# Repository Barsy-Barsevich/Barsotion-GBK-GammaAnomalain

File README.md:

# Barsotion GBK GammaAnomalain

Board computer created for "OKB Iva "Kilka"", 2024

## Parameters
- Microcontroller: ATmega328PB / LGT8X328P
- Clock frequency: 16MHz / 32MHz
- Gyroscope: external, MPU6050 (I2C)
- Barometer: external, 2x BMP388 (I2C)
- Memory: 8MB SPI NOR Flash

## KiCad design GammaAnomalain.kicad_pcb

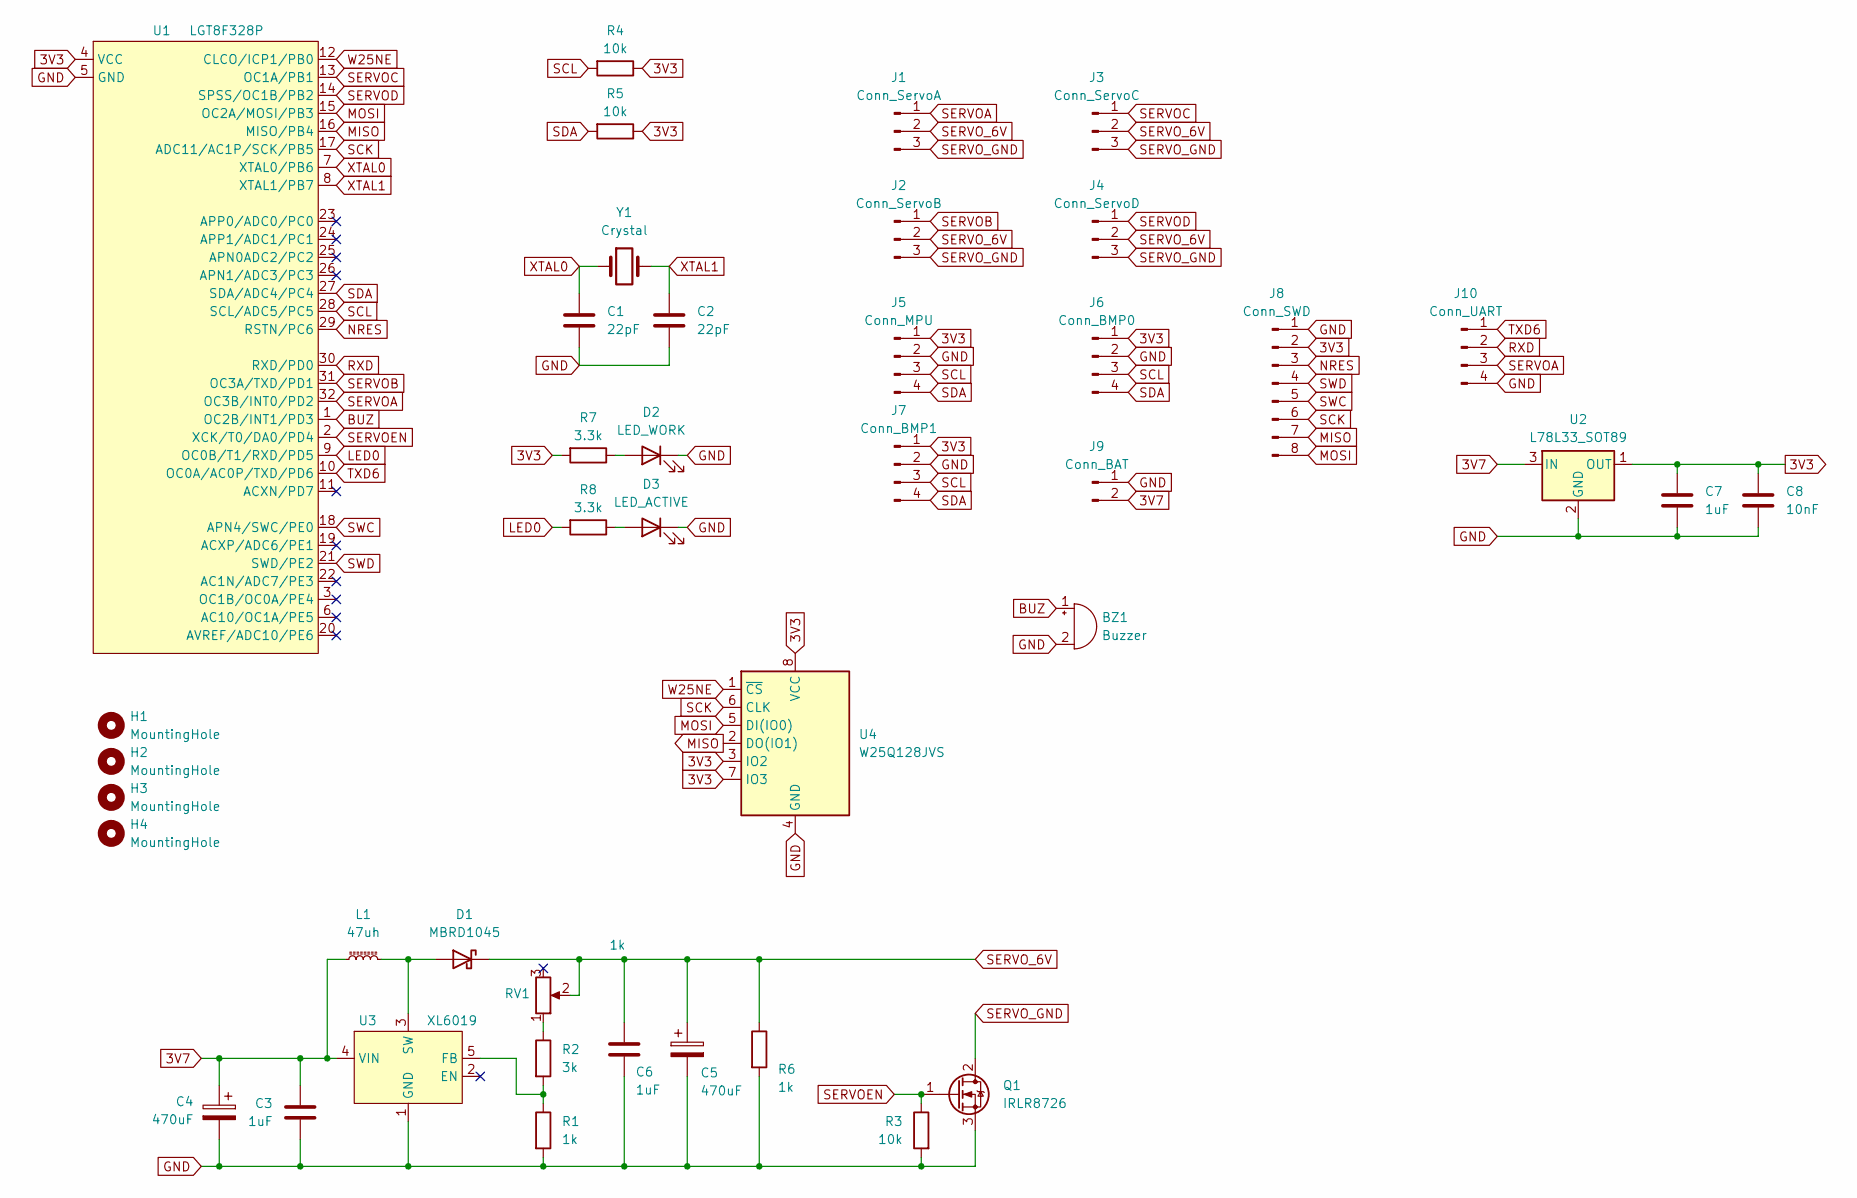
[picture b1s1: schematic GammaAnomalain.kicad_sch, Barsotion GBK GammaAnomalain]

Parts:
BZ1: Buzzer; MagneticBuzzer_ProSignal_ABI-009-RC
C1, C2: 22pF; C_0805_2012Metric
C3, C6, C7: 1uF; C_1206_3216Metric_Pad1.33x1.80mm_HandSolder
C4, C5: 470uF; CP_Radial_D8.0mm_P3.50mm
C8: 10nF; C_0805_2012Metric_Pad1.18x1.45mm_HandSolder
D1: MBRD1045; TO-252-2_TabPin1_Other2
D2: LED_WORK; LED_D3.0mm
D3: LED_ACTIVE; LED_D3.0mm
H1, H2, H3, H4: MountingHole; MountingHole_3.2mm_M3
J1: Conn_ServoA; JST_XH_B3B-XH-A_1x03_P2.50mm_Vertical
J2: Conn_ServoB; JST_XH_B3B-XH-A_1x03_P2.50mm_Vertical
J3: Conn_ServoC; JST_XH_B3B-XH-A_1x03_P2.50mm_Vertical
J4: Conn_ServoD; JST_XH_B3B-XH-A_1x03_P2.50mm_Vertical
J5: Conn_MPU; JST_XH_B4B-XH-A_1x04_P2.50mm_Vertical
J6: Conn_BMP0; JST_XH_B4B-XH-A_1x04_P2.50mm_Vertical
J7: Conn_BMP1; JST_XH_B4B-XH-A_1x04_P2.50mm_Vertical
J8: Conn_SWD; PinHeader_1x08_P2.54mm_Vertical
J9: Conn_BAT; Battery_3V7_Cable_solding_connctor
J10: Conn_UART; JST_XH_B4B-XH-A_1x04_P2.50mm_Vertical
L1: 47uh; L_Toroid_Vertical_L13.0mm_W6.5mm_P5.60mm
Q1: IRLR8726; TO-252-2
R1, R6: 1k; R_0805_2012Metric_Pad1.20x1.40mm_HandSolder
R2: 3k; R_0805_2012Metric_Pad1.20x1.40mm_HandSolder
R3, R4, R5: 10k; R_0805_2012Metric_Pad1.20x1.40mm_HandSolder
R7, R8: 3.3k; R_0805_2012Metric_Pad1.20x1.40mm_HandSolder
RV1: 1k; Potentiometer_Bourns_3296W_Vertical
U1: LGT8F328P; LQFP-32_7x7mm_P0.8mm
U2: L78L33_SOT89; SOT-89-3
U3: XL6019; TO-263-5_TabPin3
U4: W25Q128JVS; DIP-8_W7.62mm_LongPads
Y1: Crystal; Crystal_HC49-4H_Vertical

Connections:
3V3: C7.1, C8.1, J5.1, J6.1, J7.1, J8.2, R4.1, R5.1, R7.2, U1.4 (VCC), U2.1 (OUT), U4.3 (IO2), U4.7 (IO3), U4.8 (VCC)
3V7: C3.1, C4.1, J9.2, L1.1, U2.3 (IN), U3.4 (VIN)
BUZ: BZ1.1 (+), U1.1 (OC2B/INT1/PD3)
GND: BZ1.2 (-), C1.2, C2.2, C3.2, C4.2, C5.2, C6.2, C7.2, C8.2, D2.1 (K), D3.1 (K), J5.2, J6.2, J7.2, J8.1, J9.1, J10.4, Q1.3 (S), R1.2, R3.2, R6.2, U1.5 (GND), U2.2 (GND), U3.1 (GND), U4.4 (GND); also elsewhere on the board
LED0: R8.2, U1.9 (OC0B/T1/RXD/PD5)
MISO: J8.7, U1.16 (MISO/PB4), U4.2 (DO(IO1))
MOSI: J8.8, U1.15 (OC2A/MOSI/PB3), U4.5 (DI(IO0))
NRES: J8.3, U1.29 (RSTN/PC6)
unnamed: D1.2 (A), L1.2, U3.3 (SW)
unnamed: D2.2 (A), R7.1
unnamed: D3.2 (A), R8.1
unnamed: R2.1, RV1.1
unnamed: R1.1, R2.2, U3.5 (FB)
RXD: J10.2, U1.30 (RXD/PD0); also elsewhere on the board
SCK: J8.6, U1.17 (ADC11/AC1P/SCK/PB5), U4.6 (CLK)
SCL: J5.3, J6.3, J7.3, R4.2, U1.28 (SCL/ADC5/PC5)
SDA: J5.4, J6.4, J7.4, R5.2, U1.27 (SDA/ADC4/PC4)
SERVOA: J1.1, J10.3, U1.32 (OC3B/INT0/PD2); also elsewhere on the board
SERVOB: J2.1, U1.31 (OC3A/TXD/PD1)
SERVOC: J3.1, U1.13 (OC1A/PB1)
SERVOD: J4.1, U1.14 (SPSS/OC1B/PB2)
SERVOEN: Q1.1 (G), R3.1, U1.2 (XCK/T0/DA0/PD4)
SERVO_6V: C5.1, C6.1, D1.1 (K), J1.2, J2.2, J3.2, J4.2, R6.1, RV1.2
SERVO_GND: J1.3, J2.3, J3.3, J4.3, Q1.2 (D)
SWC: J8.5, U1.18 (APN4/SWC/PE0)
SWD: J8.4, U1.21 (SWD/PE2)
TXD6: J10.1, U1.10 (OC0A/AC0P/TXD/PD6); also elsewhere on the board
W25NE: U1.12 (CLCO/ICP1/PB0), U4.1 (~CS)
XTAL0: C1.1, U1.7 (XTAL0/PB6), Y1.1
XTAL1: C2.1, U1.8 (XTAL1/PB7), Y1.2

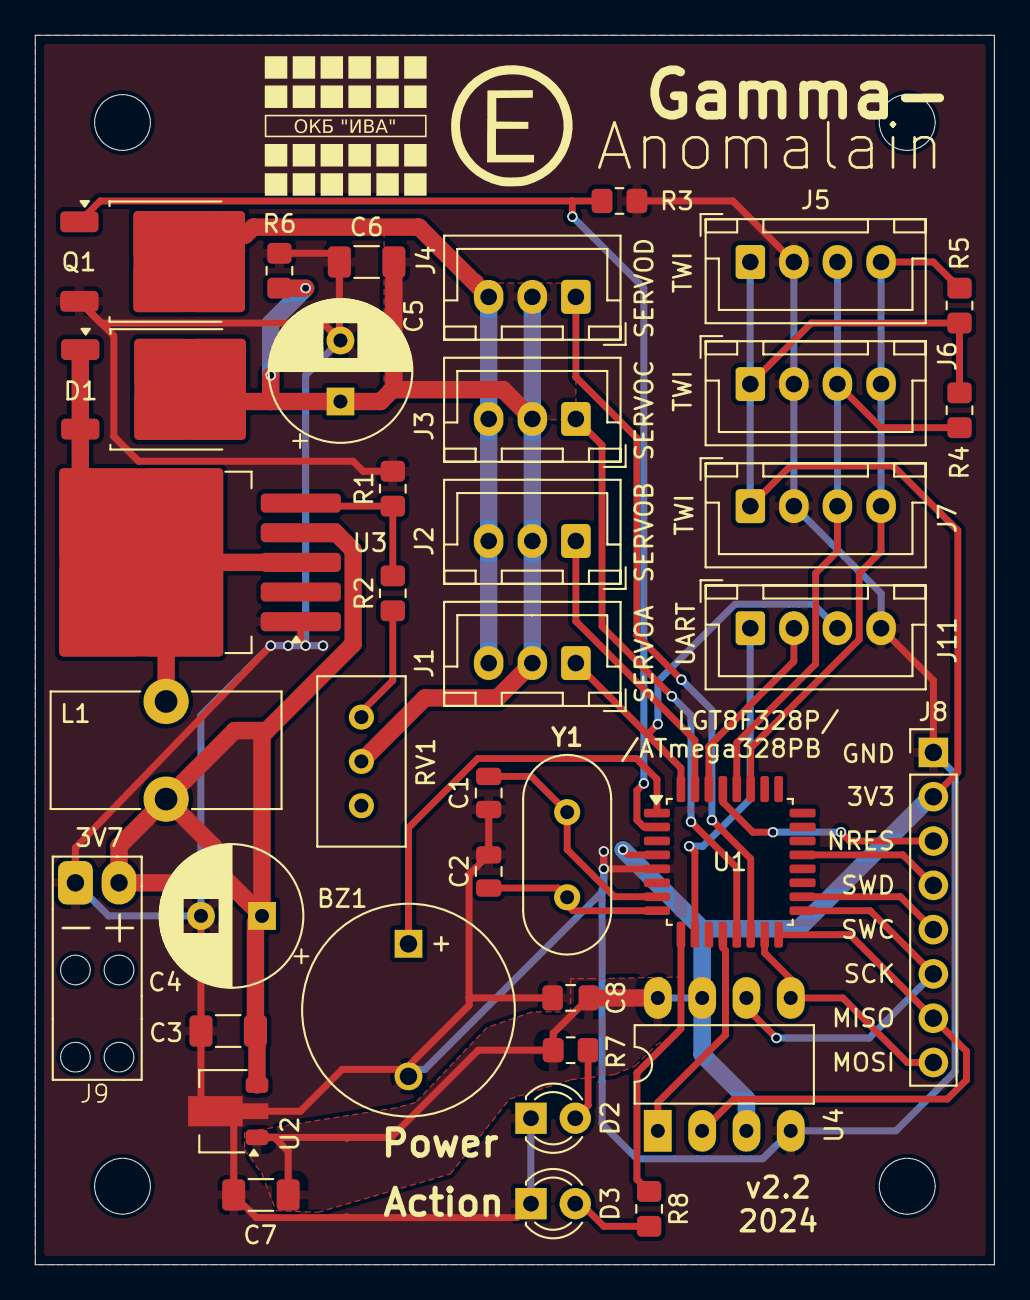
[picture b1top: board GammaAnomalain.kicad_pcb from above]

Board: 2 copper layers, 55.0 x 70.5 mm, 42 parts (0 on the bottom side), 30 nets.

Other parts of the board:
J11: Conn_UART; JST_XH_B4B-XH-A_1x04_P2.50mm_Vertical

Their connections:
GND: J11.4; also elsewhere on the board
RXD: J11.2; also elsewhere on the board
SERVOA: J11.3; also elsewhere on the board
TXD6: J11.1; also elsewhere on the board

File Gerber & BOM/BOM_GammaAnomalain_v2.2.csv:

Reference,Value,Footprint,Description
BZ1,Buzzer,Buzzer_Beeper:MagneticBuzzer_ProSignal_ABI-009-RC,"Buzzer, polarized"
C1,22pF,Capacitor_SMD:C_0805_2012Metric,Unpolarized capacitor
C2,22pF,Capacitor_SMD:C_0805_2012Metric,Unpolarized capacitor
C3,1uF,Capacitor_SMD:C_1206_3216Metric_Pad1.33x1.80mm_HandSolder,Unpolarized capacitor
C4,470uF,Capacitor_THT:CP_Radial_D8.0mm_P3.50mm,Polarized capacitor
C5,470uF,Capacitor_THT:CP_Radial_D8.0mm_P3.50mm,Polarized capacitor
C6,1uF,Capacitor_SMD:C_1206_3216Metric_Pad1.33x1.80mm_HandSolder,Unpolarized capacitor
C7,1uF,Capacitor_SMD:C_1206_3216Metric_Pad1.33x1.80mm_HandSolder,Unpolarized capacitor
C8,10nF,Capacitor_SMD:C_0805_2012Metric_Pad1.18x1.45mm_HandSolder,Unpolarized capacitor
D1,MBRD1045,CustomPackage:TO-252-2_TabPin1_Other2,Schottky Rectifier 45V 10(150)A TO252-2
D2,LED_WORK,LED_THT:LED_D3.0mm,Light emitting diode
D3,LED_ACTIVE,LED_THT:LED_D3.0mm,Light emitting diode
H1,MountingHole,MountingHole:MountingHole_3.2mm_M3,Mounting Hole without connection
H2,MountingHole,MountingHole:MountingHole_3.2mm_M3,Mounting Hole without connection
H3,MountingHole,MountingHole:MountingHole_3.2mm_M3,Mounting Hole without connection
H4,MountingHole,MountingHole:MountingHole_3.2mm_M3,Mounting Hole without connection
J1,Conn_ServoA,Connector_JST:JST_XH_B3B-XH-A_1x03_P2.50mm_Vertical,"Generic connector, single row, 01x03, script generated"
J2,Conn_ServoB,Connector_JST:JST_XH_B3B-XH-A_1x03_P2.50mm_Vertical,"Generic connector, single row, 01x03, script generated"
J3,Conn_ServoC,Connector_JST:JST_XH_B3B-XH-A_1x03_P2.50mm_Vertical,"Generic connector, single row, 01x03, script generated"
J4,Conn_ServoD,Connector_JST:JST_XH_B3B-XH-A_1x03_P2.50mm_Vertical,"Generic connector, single row, 01x03, script generated"
J5,Conn_MPU,Connector_JST:JST_XH_B4B-XH-A_1x04_P2.50mm_Vertical,"Generic connector, single row, 01x04, script generated"
J6,Conn_BMP0,Connector_JST:JST_XH_B4B-XH-A_1x04_P2.50mm_Vertical,"Generic connector, single row, 01x04, script generated"
J7,Conn_BMP1,Connector_JST:JST_XH_B4B-XH-A_1x04_P2.50mm_Vertical,"Generic connector, single row, 01x04, script generated"
J8,Conn_SWD,Connector_PinHeader_2.54mm:PinHeader_1x08_P2.54mm_Vertical,"Generic connector, single row, 01x08, script generated"
J9,Conn_BAT,CustomConnectors:Battery_3V7_Cable_solding_connctor,"Generic connector, single row, 01x02, script generated"
J10,Conn_UART,Connector_JST:JST_XH_B4B-XH-A_1x04_P2.50mm_Vertical,"Generic connector, single row, 01x04, script generated"
L1,47uh,Inductor_THT:L_Toroid_Vertical_L13.0mm_W6.5mm_P5.60mm,"Inductor with ferrite core, small symbol"
Q1,IRLR8726,Package_TO_SOT_SMD:TO-252-2,"1.7A Id, 500V Vds, CoolMOS N-Channel Power MOSFET, 3Ohm Ron, 4.3nC Qg (typ), TO-252-2"
R1,1k,Resistor_SMD:R_0805_2012Metric_Pad1.20x1.40mm_HandSolder,Resistor
R2,3k,Resistor_SMD:R_0805_2012Metric_Pad1.20x1.40mm_HandSolder,Resistor
R3,10k,Resistor_SMD:R_0805_2012Metric_Pad1.20x1.40mm_HandSolder,Resistor
R4,10k,Resistor_SMD:R_0805_2012Metric_Pad1.20x1.40mm_HandSolder,Resistor
R5,10k,Resistor_SMD:R_0805_2012Metric_Pad1.20x1.40mm_HandSolder,Resistor
R6,1k,Resistor_SMD:R_0805_2012Metric_Pad1.20x1.40mm_HandSolder,Resistor
R7,3.3k,Resistor_SMD:R_0805_2012Metric_Pad1.20x1.40mm_HandSolder,Resistor
R8,3.3k,Resistor_SMD:R_0805_2012Metric_Pad1.20x1.40mm_HandSolder,Resistor
RV1,1k,Potentiometer_THT:Potentiometer_Bourns_3296W_Vertical,Potentiometer
U1,LGT8F328P,Package_QFP:LQFP-32_7x7mm_P0.8mm,8-bit microcontroller based on AVR architecture
U2,L78L33_SOT89,Package_TO_SOT_SMD:SOT-89-3,"Positive 100mA 30V Linear Regulator, Fixed Output 3.3V, SOT-89"
U3,XL6019,Package_TO_SOT_SMD:TO-263-5_TabPin3,DC-DC Pull-up converter
U4,W25Q128JVS,Package_DIP:DIP-8_W7.62mm_LongPads,"128Mb Serial Flash Memory, Standard/Dual/Quad SPI, SOIC-8"
Y1,Crystal,Crystal:Crystal_HC49-4H_Vertical,Two pin crystal

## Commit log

2025-03-06 gitignore creation
2025-03-06 gitignore update
2025-03-06 Create LICENSE
